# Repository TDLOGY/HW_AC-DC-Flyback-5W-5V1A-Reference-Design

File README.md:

# AC-DC-Flyback-5W-5V1A-Reference-Design
AC DC Flyback 5W 5V1A Reference Design
---

- __[Linh Kiện Thủ Đức](https://linhkienthuduc.com/)__ - Electronics shop in Viet Nam

You will like those projects!
## Please note that this project just for learning basic of AC-DC power supply purpose, will not care about safety standard. Only use it for application which need basic safety!!!
---

### Reference Design for flyback AC-DC circuit with 5W power output 5V & 1A 8-)
#### Details about the design procedure you can find here - __[Design guideline (Vietnamese)](https://linhkienthuduc.com/chia-se-thiet-ke-mau-va-tinh-toan-thiet-ke-mach-nguon-xung-flyback-ac-dc-5w-5v-1a-cho-cac-ung-dung-cong-suat-thap)__

Download Schematic PDF with detail footprint, value, part number **( you should download it and use Foxit Reader to click on the component to see it)**
__[Download here](https://github.com/TDLOGY/AC-DC-Flyback-5W-5V1A-Reference-Design/blob/main/5V2A_PS_EE1310_Schematic.pdf)__

Note 1: **Reference value of resistor can be adjust base on the design to have exactly value**

Note 2: **The transformer used in design is not used for higher voltage output ex 9V,12v,15V...**

#### Picture reference

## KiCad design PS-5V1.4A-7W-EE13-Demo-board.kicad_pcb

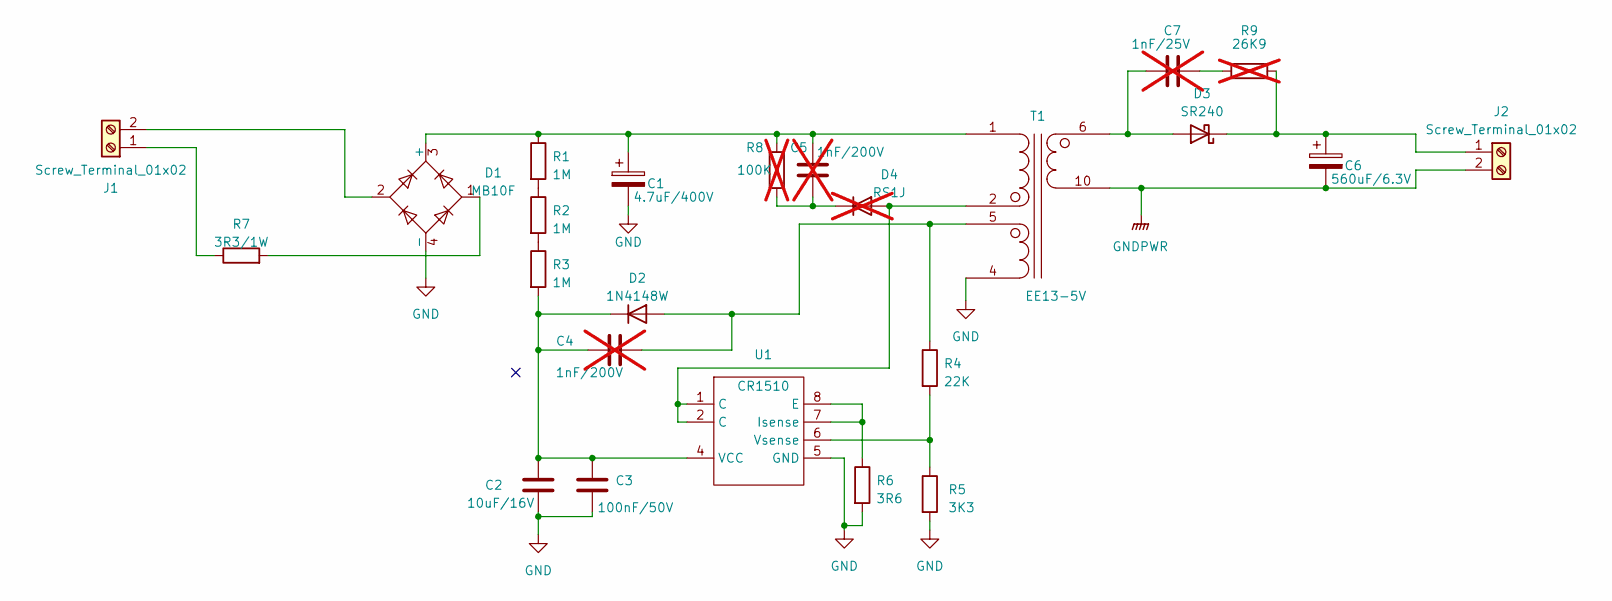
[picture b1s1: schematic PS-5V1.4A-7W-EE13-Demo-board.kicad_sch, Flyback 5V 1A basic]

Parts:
C1: 4.7uF/400V; CP_Radial_D8.0mm_P3.50mm
C2: 10uF/16V; C_0805_2012Metric
C3: 100nF/50V; C_0603_1608Metric
C4, C5: 1nF/200V; C_0805_2012Metric; not fitted
C6: 560uF/6.3V; CP_Radial_D6.3mm_P2.50mm
C7: 1nF/25V; C_0603_1608Metric; not fitted
D1: MB10F; TO-269AA
D2: 1N4148W; D_SOD-123
D3: SR240; D_SMA
D4: RS1J; D_SMA; not fitted
J1, J2: Screw_Terminal_01x02; TerminalBlock_bornier-2_P5.08mm
R1, R2, R3: 1M; R_0603_1608Metric
R4: 22K; R_0603_1608Metric
R5: 3K3; R_0603_1608Metric
R6: 3R6; R_1206_3216Metric
R7: 3R3/1W; R_Radial_Power_1W-12x4.5
R8: 100K; R_1206_3216Metric; not fitted
R9: 26K9; R_0603_1608Metric; not fitted
T1: EE13-5V; BOBBIN_EE13_4_2
U1: CR1510; SOIC-8-N3_3.9x4.9mm_P1.27mm

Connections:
GND: C1.2, C2.2, C3.2, D1.4 (-), R5.2, R6.2, T1.4 (GND), U1.5 (GND)
GNDPWR: C6.2, J2.2, T1.10
unnamed: C7.2, R9.1
unnamed: C1.1, C5.2, D1.3 (+), R1.1, R8.1, T1.1
unnamed: D1.1, R7.2
unnamed: C4.2, D2.2 (A), R4.1, T1.5 (Aux)
unnamed: C2.1, C3.1, C4.1, D2.1 (K), R3.2, U1.4 (VCC)
unnamed: C7.1, D3.2 (A), T1.6
unnamed: C6.1, D3.1 (K), J2.1, R9.2
unnamed: D4.2 (A), T1.2 (AB), U1.1 (C), U1.2 (C)
unnamed: C5.1, D4.1 (K), R8.2
unnamed: J1.1, R7.1
unnamed: D1.2, J1.2
unnamed: R1.2, R2.1
unnamed: R2.2, R3.1
unnamed: R6.1, U1.7 (Isense), U1.8 (E)
unnamed: R4.2, R5.1, U1.6 (Vsense)

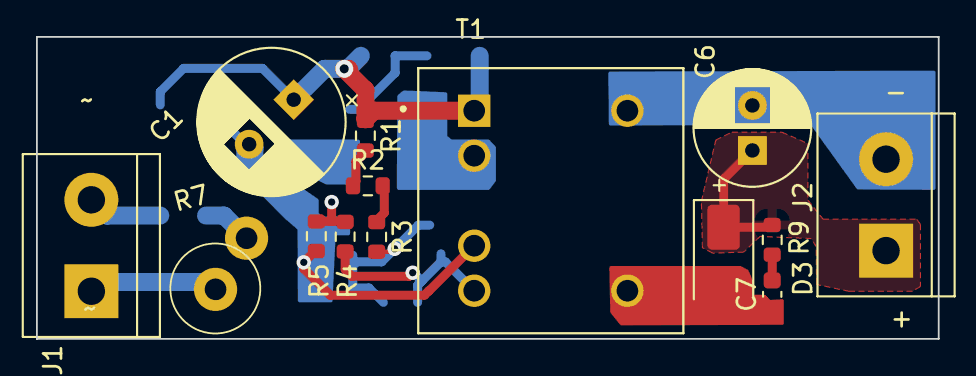
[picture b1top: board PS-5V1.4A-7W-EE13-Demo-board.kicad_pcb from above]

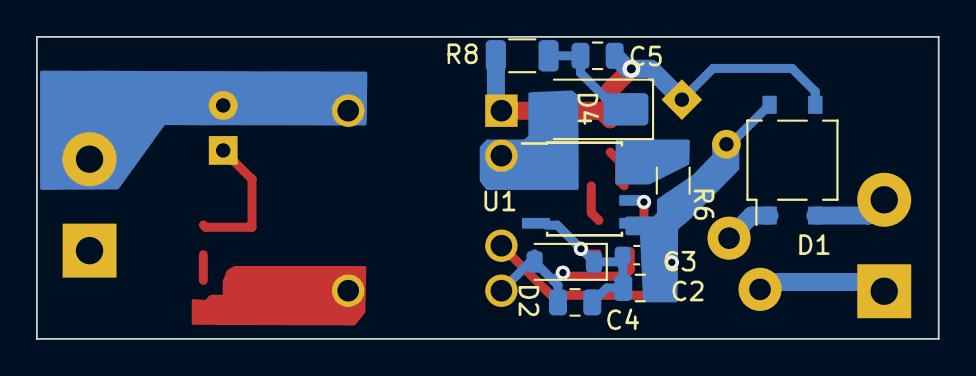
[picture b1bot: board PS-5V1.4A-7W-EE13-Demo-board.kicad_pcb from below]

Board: 2 copper layers, 50.1 x 16.8 mm, 24 parts (10 on the bottom side), 17 nets.

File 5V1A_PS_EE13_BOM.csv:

"Reference","Value","Footprint","LINK Mua","LKTD PN","Qty"
"T1","EE13-5V","0_Custom:BOBBIN_EE13_4_2","https://linhkienthuduc.com/bien-ap-xung-ee13-5v-1a-5w","TD0683","1"
"U1","CR1510","Package_SO:SOIC-8-N3_3.9x4.9mm_P1.27mm","https://linhkienthuduc.com/cr1510-ic-dieu-khien-nguon-flyback-5w","TD0594","1"
"D3","SR240","Diode_SMD:D_SMA","https://linhkienthuduc.com/sr240-ss24-sma-diode-schottky-2a-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","TD0593","1"
"C3","100nF/50V","Capacitor_SMD:C_0603_1608Metric","https://linhkienthuduc.com/tu-dien-ceramic-100nf-50v-0603","TD0582","1"
"C2","10uF/16V","Capacitor_SMD:C_0805_2012Metric","https://linhkienthuduc.com/tu-dien-ceramic-10uf-16v-0805","TD0581","1"
"R1-R3","1M","Resistor_SMD:R_0603_1608Metric","https://linhkienthuduc.com/dien-tro-1m-ohm-0603-5","TD0578","3"
"J1, J2","Screw_Terminal_01x02","TerminalBlock:TerminalBlock_bornier-2_P5.08mm","https://linhkienthuduc.com/kf301-2-v-domino-2-chan-thang-5-0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","TD0478","2"
"C1","4.7uF/400V","Capacitor_THT:CP_Radial_D8.0mm_P3.50mm","https://linhkienthuduc.com/tu-hoa-4-7uf-400v-8x13mm","TD0464","1"
"D2","1N4148W","Diode_SMD:D_SOD-123","https://linhkienthuduc.com/diode-1n4148w-75v-150ma","TD0196","1"
"R6","3R6","Resistor_SMD:R_1206_3216Metric","https://linhkienthuduc.com/dien-tro-3-6-ohm-0805-1","TD0188","1"
"R7","3R3/2W","0_Custom:R_Radial_Power_1W-12x4.5","https://linhkienthuduc.com/dien-tro-3-3-ohm-1w-5","TD0100","1"
"D1","MB10F","Package_TO_SOT_SMD:TO-269AA","https://linhkienthuduc.com/mb10f-cau-chinh-luu-1kv-0-5a-sop-4","SP000212","1"
"R5","3K3","Resistor_SMD:R_0603_1608Metric","https://linhkienthuduc.com/dien-tro-3-3-kohm-0603-5","SP000187","1"
"C6","560uF/6.3V","Capacitor_THT:CP_Radial_D6.3mm_P2.50mm","https://linhkienthuduc.com/tu-nhom-cam-xuyen-lo-560uf-6-3v-6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","SP000110","1"
"R8","100K","Resistor_SMD:R_1206_3216Metric","https://www.thegioiic.com/dien-tro-100-kohm-1206-5","","1"
"R4, R9","26K9","Resistor_SMD:R_0603_1608Metric","https://www.thegioiic.com/dien-tro-24-kohm-0603-5","","2"
"D4","RS1J","Diode_SMD:D_SMA","https://linhkienthuduc.com/rs1m-sma-fast-diode-1a-1000v","","1"
"C7","1nF/25V","Capacitor_SMD:C_0603_1608Metric","","","1"
"C4, C5","1nF/200V","Capacitor_SMD:C_0805_2012Metric","","","2"

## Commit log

2023-03-17 Update Schematic
2023-03-17 3d Picture
2023-03-17 Transformer Library Kicad and 3d step model
2023-03-17 Picture schematic
2023-03-17 Bill of material
2023-03-19 Schematic PDF
2023-03-19 Schematic picture
2023-03-19 Schematic pciture
2023-03-19 Source file design in kicad
2023-03-24 Update schematic and footprint
